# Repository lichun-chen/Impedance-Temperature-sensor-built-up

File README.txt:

//This project is the Final version code used in Z_T_sensor
The Z_T_sensor is designed to monitor the impedance and temperature of mortar samples installed in the field environments. Several multiplers, a real-time colock, a SD card is embaded into this circuit to get the real-time reading of the field samples.
License
OSU GENERAL PUBLIC LICENSE V1.0

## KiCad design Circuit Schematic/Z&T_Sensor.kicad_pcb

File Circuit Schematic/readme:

This is the circuit layout in KiCAD

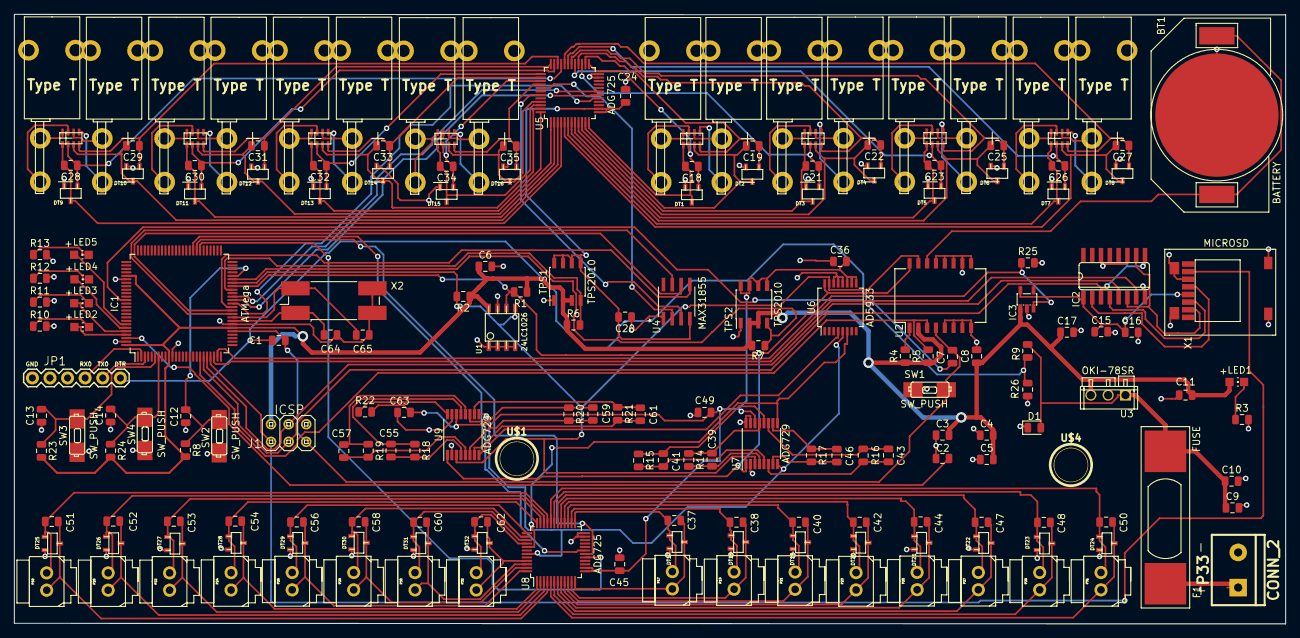
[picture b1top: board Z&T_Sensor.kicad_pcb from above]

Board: 2 copper layers, 183.6 x 88.0 mm, 196 parts (0 on the bottom side), 169 nets.

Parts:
BT1: BATTERY; Battery_20mm_coincell
C1, C2, C3, C4, C5, C6, C7, C8, C12, C13, C14, C15, C17: 0.1uF; C_0805_2012Metric
C9: 10u; C_0805_2012Metric
C10, C11: 0.1u; C_0805_2012Metric
C16: 10uF; C_0805_2012Metric
C18, C19, C20, C21, C22, C23, C24, C25, C26, C27, C28, C29, C30, C31, C32, C33, C34, C35, C36, C37, C38, C39, C40, C41, C42, C43, C44, C45, C46, C47, C48, C49, C50, C51, C52, C53, C54, C55, C56, C57, C58, C59, C60, C61, C62, C63: .01uF; C_0805_2012Metric
C64, C65: 22pF; C_0805_2012Metric
D1: DIODE; D_0805_2012Metric
DT1, DT2, DT3, DT4, DT5, DT6, DT7, DT8, DT9, DT10, DT11, DT12, DT13, DT14, DT15, DT16, DT17, DT18, DT19, DT20, DT21, DT22, DT23, DT24, DT25, DT26, DT27, DT28, DT29, DT30, DT31, DT32: TVSARRAY
F1: FUSE; FUSE_5x25
FB1, FB2, FB3, FB4, FB5, FB6, FB7, FB8: FEARRAY
IC1: ATMEGA2560-A; ATMega_TQFP-100_14x14mm_P0.5mm
IC2: 4050D; SO16
IC3: LP298XS; SOT23-5L
J1: ICSP; ICSP-pinhead-1-2X03
JP1: FTDI Basic; 1X06
LED1, LED2, LED3, LED4, LED5: LED; CHIP-LED0805
P1, P2, P3, P4, P5, P6, P7, P8, P9, P10, P11, P12, P13, P14, P15, P16: CONN_4; thermocouple-connector
P17, P18, P19, P20, P21, P22, P23, P24, P25, P26, P27, P28, P29, P30, P31, P32: CONN_2; Z_COMBICON2
P33: CONN_2; bornier2_V
R1, R2, R22, R26: 10K; R_0805_2012Metric
R3, R4, R5, R10, R11, R12, R13: 330; R_0805_2012Metric
R6, R7, R25: 100K; R_0805_2012Metric
R8, R9, R23, R24: 47k; R_0805_2012Metric
R14, R18: 560; R_0805_2012Metric
R15, R19: 1000; R_0805_2012Metric
R16, R20: 1500; R_0805_2012Metric
R17, R21: 2000; R_0805_2012Metric
SW1, SW2, SW3, SW4: SW_PUSH; SWITCH_2padsmd
TPS1, TPS2: TPS2010; TPS2010_SOIC-8-N8_3.9x4.9mm_P1.27mm
U1: 24LC1026
U2: DS3231; SOIC-16W_7.5x12.8mm_P1.27mm
U3: OKI-78SR
U4: MAX31855; MAX31855TASA&plus_T
U5, U8: ADG725; ADG725_TQFP-48-1EP_7x7mm_P0.5mm_EP3.5x3.5mm
U6: AD5933; AD5933_SSOP-16_5.3x6.2mm_P0.65mm
U7, U9: ADG729; ADG729_TSSOP-16_4.4x5mm_P0.65mm
U$1, U$4: FIDUCIAL; DrillHole_1pin
X1: MICROSD; MicroSD_2
X2: CRYSTAL; Crystal_SMD_SeikoEpson_MA506-4Pin_12.7x5.1mm

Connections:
+12V: F1.1, P33.1
/MISO: IC1.22, J1.1, X1.7
/MOSI: IC1.21, IC2.5, J1.4
/RX0: IC1.2, JP1.3
/SCK: IC1.20, IC2.3, IC2.9, J1.3
/SD_CS: IC1.23, IC2.7
/SD_Card/+3V3: C15.1, C16.1, IC2.1, IC3.5, X1.4
/SD_EN: IC1.24, IC3.3, R25.1
/Switch_LED/SWITCH1: C12.2, IC1.46, R8.1, SW2.2
/Switch_LED/SWITCH2: C13.2, IC1.6, R23.1, SW3.2
/Switch_LED/SWITCH3: C14.2, IC1.7, R24.1, SW4.2
/TX0: IC1.3, JP1.2
/T_sensor/5V: C20.2, C24.1, TPS1.5, TPS1.6, TPS1.7, TPS1.8, U4.4, U5.13, U5.14
/T_sensor/DIN: IC1.39, U5.18
/T_sensor/MISO: IC1.35, U4.7
/T_sensor/SCK: IC1.37, U4.5
/T_sensor/SCLK: IC1.40, U5.19
/T_sensor/SS: IC1.36, U4.6
/T_sensor/SYNC: IC1.38, U5.17
/T_sensor/ThermocoupleBreakout/T1a: FB1.5, P1.1
/T_sensor/ThermocoupleBreakout/T1b: FB1.6, P1.2
/T_sensor/ThermocoupleBreakout/T2a: FB1.7, P3.1
/T_sensor/ThermocoupleBreakout/T2b: FB1.8, P3.2
/T_sensor/ThermocoupleBreakout/T3a: FB2.5, P5.1
/T_sensor/ThermocoupleBreakout/T3b: FB2.6, P5.2
/T_sensor/ThermocoupleBreakout/T4a: FB2.7, P7.1
/T_sensor/ThermocoupleBreakout/T4b: FB2.8, P7.2
/T_sensor/ThermocoupleBreakout/T5a: FB3.5, P9.1
/T_sensor/ThermocoupleBreakout/T5b: FB3.6, P9.2
/T_sensor/ThermocoupleBreakout/T6a: FB3.7, P11.1
/T_sensor/ThermocoupleBreakout/T6b: FB3.8, P11.2
/T_sensor/ThermocoupleBreakout/T7a: FB4.5, P13.1
/T_sensor/ThermocoupleBreakout/T7b: FB4.6, P13.2
/T_sensor/ThermocoupleBreakout/T8a: FB4.7, P15.1
/T_sensor/ThermocoupleBreakout/T8b: FB4.8, P15.2
/T_sensor/ThermocoupleBreakout/T9a: FB5.5, P2.1
/T_sensor/ThermocoupleBreakout/T9b: FB5.6, P2.2
/T_sensor/ThermocoupleBreakout/T10a: FB5.7, P4.1
/T_sensor/ThermocoupleBreakout/T10b: FB5.8, P4.2
/T_sensor/ThermocoupleBreakout/T11a: FB6.5, P6.1
/T_sensor/ThermocoupleBreakout/T11b: FB6.6, P6.2
/T_sensor/ThermocoupleBreakout/T12a: FB6.7, P8.1
/T_sensor/ThermocoupleBreakout/T12b: FB6.8, P8.2
/T_sensor/ThermocoupleBreakout/T13a: FB7.5, P10.1
/T_sensor/ThermocoupleBreakout/T13b: FB7.6, P10.2
/T_sensor/ThermocoupleBreakout/T14a: FB7.7, P12.1
/T_sensor/ThermocoupleBreakout/T14b: FB7.8, P12.2
/T_sensor/ThermocoupleBreakout/T15a: FB8.5, P14.1
/T_sensor/ThermocoupleBreakout/T15b: FB8.6, P14.2
/T_sensor/ThermocoupleBreakout/T16a: FB8.7, P16.1
/T_sensor/ThermocoupleBreakout/T16b: FB8.8, P16.2
/Z_sensor/5V: C36.2, C45.2, C49.2, C63.2, R22.2, TPS2.5, TPS2.6, TPS2.7, TPS2.8, U6.9, U6.10, U6.11, U7.14, U8.13, U8.14, U9.14
/Z_sensor/DIN: IC1.58, U8.18
/Z_sensor/SCLK: IC1.59, U8.19
/Z_sensor/SYNC: IC1.57, U8.17
/Z_sensor/z_impedance/Z1A: C37.2, DT17.2, P17.1, U8.12
/Z_sensor/z_impedance/Z1B: C37.1, DT17.1, P17.2, U8.25
/Z_sensor/z_impedance/Z2A: C38.2, DT18.2, P19.1, U8.11
/Z_sensor/z_impedance/Z2B: C38.1, DT18.1, P19.2, U8.26
/Z_sensor/z_impedance/Z3A: C40.2, DT19.2, P21.1, U8.10
/Z_sensor/z_impedance/Z3B: C40.1, DT19.1, P21.2, U8.27
/Z_sensor/z_impedance/Z4A: C42.2, DT20.2, P23.1, U8.9
/Z_sensor/z_impedance/Z4B: C42.1, DT20.1, P23.2, U8.28
/Z_sensor/z_impedance/Z5A: C44.2, DT21.2, P25.1, U8.8
/Z_sensor/z_impedance/Z5B: C44.1, DT21.1, P25.2, U8.29
/Z_sensor/z_impedance/Z6A: C47.2, DT22.2, P27.1, U8.7
/Z_sensor/z_impedance/Z6B: C47.1, DT22.1, P27.2, U8.30
/Z_sensor/z_impedance/Z7A: C48.2, DT23.2, P29.1, U8.6
/Z_sensor/z_impedance/Z7B: C48.1, DT23.1, P29.2, U8.31
/Z_sensor/z_impedance/Z8A: C50.2, DT24.2, P31.1, U8.5
/Z_sensor/z_impedance/Z8B: C50.1, DT24.1, P31.2, U8.32
/Z_sensor/z_impedance/Z9A: C51.2, DT25.2, P18.1, U8.4
/Z_sensor/z_impedance/Z9B: C51.1, DT25.1, P18.2, U8.33
/Z_sensor/z_impedance/Z10A: C52.2, DT26.2, P20.1, U8.3
/Z_sensor/z_impedance/Z10B: C52.1, DT26.1, P20.2, U8.34
/Z_sensor/z_impedance/Z11A: C53.2, DT27.2, P22.1, U8.2
/Z_sensor/z_impedance/Z11B: C53.1, DT27.1, P22.2, U8.35
/Z_sensor/z_impedance/Z12A: C54.2, DT28.2, P24.1, U8.1
/Z_sensor/z_impedance/Z12B: C54.1, DT28.1, P24.2, U8.36
/Z_sensor/z_impedance/Z13A: C56.2, DT29.2, P26.1, U8.48
/Z_sensor/z_impedance/Z13B: C56.1, DT29.1, P26.2, U8.37
/Z_sensor/z_impedance/Z14A: C58.2, DT30.2, P28.1, U8.47
/Z_sensor/z_impedance/Z14B: C58.1, DT30.1, P28.2, U8.38
/Z_sensor/z_impedance/Z15A: C60.2, DT31.2, P30.1, U8.46
/Z_sensor/z_impedance/Z15B: C60.1, DT31.1, P30.2, U8.39
/Z_sensor/z_impedance/Z16A: C62.2, DT32.2, P32.1, U8.45
/Z_sensor/z_impedance/Z16B: C62.1, DT32.1, P32.2, U8.40
/clock-ISP schema/INTSQW: IC1.19, R5.2, U2.3
/led/LED1: IC1.97, LED2.A
/led/LED2: IC1.96, LED3.A
/led/LED3: IC1.95, LED4.A
/led/LED4: IC1.94, LED5.A
ADBATT: IC1.87, R9.1, R26.2
DTR: C1.2, C7.2, JP1.1
GND: BT1.2, C2.2, C3.1, C4.1, C5.1, C6.2, C8.2, C9.2, C10.2, C11.2, C12.1, C13.1, C14.1, C15.2, C16.2, C17.2, C20.1, C24.2, C36.1, C45.1, C49.1, C63.1, C64.2, C65.2, D1.1, DT1.3, DT2.3, DT3.3, DT4.3, DT5.3, DT6.3, DT7.3, DT8.3, DT9.3, DT10.3, DT11.3, DT12.3, DT13.3, DT14.3, DT15.3, DT16.3, DT17.3, DT18.3, DT19.3, DT20.3, DT21.3, DT22.3, DT23.3, DT24.3, DT25.3, DT26.3, DT27.3, DT28.3, DT29.3, DT30.3, DT31.3, DT32.3, IC1.11, IC1.32, IC1.81, IC1.99, IC2.8, IC2.11, IC2.14, IC3.2, J1.6, JP1.6, P1.3, P1.4, P2.3, P2.4, P3.3, P3.4, P4.3, P4.4, P5.3, P5.4, P6.3, P6.4, P7.3, P7.4, P8.3, P8.4, P9.3, P9.4, P10.3, P10.4, P11.3, P11.4, P12.3, P12.4, P13.3, P13.4, P14.3, P14.4, P15.3, P15.4, P16.3, P16.4, P33.2, R3.2, R10.2, R11.2, R12.2, R13.2, R25.2, R26.1, SW1.1, SW2.1, SW3.1, SW4.1, TPS1.1, TPS2.1, U1.1, U1.2, U1.3, U1.4, U1.7, U2.5, U2.6, U2.7, U2.8, U2.9, U2.10, U2.11, U2.12, U2.13, U3.2, U4.1, U5.23, U5.24, U6.12, U6.13, U6.14, U7.2, U7.15, U7.16, U8.23, U8.24, U9.2, U9.15, X1.6, X1.GND1, X1.GND2, X1.GND3, X1.GND4, X2.2, X2.3
unnamed: BT1.1, U2.14
unnamed: C2.1, IC1.98
unnamed: C9.1, C10.1, D1.2, F1.2, R9.2, U3.1
unnamed: C18.1, DT1.1, FB1.2, U5.25
unnamed: C18.2, DT1.2, FB1.1, U5.12
unnamed: C19.1, DT2.1, FB1.4, U5.26
unnamed: C19.2, DT2.2, FB1.3, U5.11
unnamed: C21.1, DT3.1, FB2.2, U5.27
unnamed: C21.2, DT3.2, FB2.1, U5.10
unnamed: C22.1, DT4.1, FB2.4, U5.28
unnamed: C22.2, DT4.2, FB2.3, U5.9
unnamed: C23.1, DT5.1, FB3.2, U5.29
unnamed: C23.2, DT5.2, FB3.1, U5.8
unnamed: C25.1, DT6.1, FB3.4, U5.30
unnamed: C25.2, DT6.2, FB3.3, U5.7
unnamed: C26.1, DT7.1, FB4.2, U5.31
unnamed: C26.2, DT7.2, FB4.1, U5.6
unnamed: C27.1, DT8.1, FB4.4, U5.32
unnamed: C27.2, DT8.2, FB4.3, U5.5
unnamed: C28.1, DT9.1, FB5.2, U5.33
unnamed: C28.2, DT9.2, FB5.1, U5.4
unnamed: C29.1, DT10.1, FB5.4, U5.34
unnamed: C29.2, DT10.2, FB5.3, U5.3
unnamed: C30.1, DT11.1, FB6.2, U5.35
unnamed: C30.2, DT11.2, FB6.1, U5.2
unnamed: C31.1, DT12.1, FB6.4, U5.36
unnamed: C31.2, DT12.2, FB6.3, U5.1
unnamed: C32.1, DT13.1, FB7.2, U5.37
unnamed: C32.2, DT13.2, FB7.1, U5.48
unnamed: C33.1, DT14.1, FB7.4, U5.38
unnamed: C33.2, DT14.2, FB7.3, U5.47
unnamed: C34.1, DT15.1, FB8.2, U5.39
unnamed: C34.2, DT15.2, FB8.1, U5.46
unnamed: C35.1, DT16.1, FB8.4, U5.40
unnamed: C35.2, DT16.2, FB8.3, U5.45
unnamed: C39.1, R14.2, U7.4
unnamed: C39.2, R14.1, U7.13
unnamed: C41.1, R15.2, U7.5
unnamed: C41.2, R15.1, U7.12
unnamed: C43.1, R16.2, U7.6
unnamed: C43.2, R16.1, U7.11
unnamed: C46.1, R17.2, U7.7
unnamed: C46.2, R17.1, U7.10
unnamed: C55.1, R18.2, U9.4
unnamed: C55.2, R18.1, U9.13
unnamed: C57.1, R19.2, U9.5
unnamed: C57.2, R19.1, U9.12
unnamed: C59.1, R20.2, U9.6
unnamed: C59.2, R20.1, U9.11
unnamed: C61.1, R21.2, U9.7
unnamed: C61.2, R21.1, U9.10
unnamed: C64.1, IC1.33, X2.1
unnamed: C65.1, IC1.34, X2.4
unnamed: IC1.42, R6.2, TPS1.4
unnamed: IC1.45, R7.2, TPS2.4
unnamed: IC2.2, X1.5
unnamed: IC2.4, X1.3
unnamed: IC2.6, IC2.10, X1.2
unnamed: LED1.C, R3.1
unnamed: LED2.C, R10.1
unnamed: LED3.C, R11.1
unnamed: LED4.C, R12.1
unnamed: LED5.C, R13.1
unnamed: R4.2, U2.1
unnamed: R22.1, U9.16
unnamed: U4.2, U5.41
unnamed: U4.3, U5.43
unnamed: U6.4, U9.8
unnamed: U6.5, U7.8, U8.43, U9.9
unnamed: U6.6, U7.9, U8.41
RESET: C1.1, C7.1, IC1.30, J1.5, SW1.2, U2.4
SCL: IC1.43, R1.2, U1.6, U2.16, U6.16, U7.1, U9.1
SDA: IC1.44, R2.2, U1.5, U2.15, U6.15, U7.3, U9.3
V1: C3.2, C4.2, C5.2, C6.1, C8.1, C11.1, C17.1, IC1.10, IC1.31, IC1.80, IC1.100, IC3.1, J1.2, LED1.A, R1.1, R2.1, R4.1, R5.1, R6.1, R7.1, R8.2, R23.2, R24.2, TPS1.2, TPS1.3, TPS2.2, TPS2.3, U1.8, U2.2, U3.3

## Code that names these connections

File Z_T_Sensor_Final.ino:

//*******************************************************************************************************************************************
#include "AD5933.h"
#include "Adafruit_MAX31855.h"
#include <Wire.h>
#include <SD.h>
#include <SPI.h>
#include "Z_T_functions.h"

//*******************************************************************************************************************************************
//******************************************DEFINE Z&T measurement part**********************************************************************
Adafruit_MAX31855 THERMOcouple(MAXCLK, MAXCS, MAXDO);
Z_T_functions_Class Z_T_func;

//*******************************************************************************************************************************************
//******************************************DEFINE ADG725 code*******************************************************************************
int pinoff=128;//code to turn off all the switches of ADG725 (16 ports)
int SWITCHnum = 0;
int CALIBnum = 1;

//*******************************************************************************************************************************************
//******************************************DEFINE Battery part******************************************************************************
int BATT_VOLT = 0;

//*******************************************************************************************************************************************
//*******************************************************************************************************************************************
void setup()
{
  Wire.begin();        // join i2c bus (address optional for master)   
  Serial.begin(9600);
  while (!Serial) delay(1); // wait for Serial on Leonardo/Zero, etc

  //set the pins for LEDS
  pinMode(LED2, OUTPUT);
  pinMode(LED3, OUTPUT);
  pinMode(LED4, OUTPUT);
  pinMode(LED5, OUTPUT);
  digitalWrite(LED2, LOW);
  digitalWrite(LED3, LOW);
  digitalWrite(LED4, LOW);
  digitalWrite(LED5, LOW);
  
  //set pin mode for multiplexers_resistors
  pinMode(SS_Z, OUTPUT);
  pinMode(SCLK_Z, OUTPUT); 
  pinMode(MOSI_Z, OUTPUT);
  //set the pin mode for multiplexer_temperature
  pinMode(SS_T, OUTPUT);
  pinMode(SCLK_T, OUTPUT); 
  pinMode(MOSI_T, OUTPUT);
  
  //SD Card Initialization
  pinMode(SDCard_EN,OUTPUT);// enable voltage converter (define as asigned in the KiCAD file)
  digitalWrite(SDCard_EN, HIGH);// enable voltage converter (define as asigned in the KiCAD file)
  pinMode(SD_CS,OUTPUT); 
  //SD card can be only initialized once, multiple initializations result to failure. so must leave this part in the setup function, not in the loop function.
  if (!SD.begin(SD_CS))
    { // if the SD card is not put right, then do nothing
      Serial.println("SD Card Initialization Failed!"); 
      digitalWrite(LED4,HIGH); // Turn on the LED4 as a sign for SD card failed.
    }

  //set TPS2010 EN pin
  pinMode(TPSEN_Z, OUTPUT);
  pinMode(TPSEN_T, OUTPUT);
  //TUEN OFF THE TPS2010 SWITCH at the setup beginning
  digitalWrite(TPSEN_Z, HIGH); // LOW turns on the power; High turns off the power
  digitalWrite(TPSEN_T, HIGH); // LOW turns on the power; High turns off the power
  
  delay(100);
}
//*****************************************************************************************************************************************************
void loop()
{
  // GET THE VOLTAGE OF THE BATTERY AT THE BEGINNING OF EACH LOOP
  BATT_VOLT = Z_T_func.Batt_analogread();
  if (BATT_VOLT < Batt_Low) // if the battery is low then do nothing
  {delay(1800000); /*delay 30mins */ }
  else {     
      //****************************************************************************************************************************************************
      //Turn on TPS2010 switch. set the EN pin for TPSEN_Z, TPSEN_T
      digitalWrite(TPSEN_Z, LOW); // LOW turns on the power; High turns off the power
      digitalWrite(TPSEN_T, LOW); // LOW turns on the power; High turns off the power
              
      //close all switch pins of ADG729 before measurement
      Z_T_func.SwiChoi_Z(0, ADDRESS_SwiCalib);// close all switch pins of impedance calibration
      Z_T_func.SwiChoi_Z(0, ADDRESS_SwiRFB);// close all switch pins of RFB resistor
      //close all switch pins of ADG725 (16 ports) before measurement
      Z_T_func.Switch_Z(pinoff);
      Z_T_func.Switch_T(pinoff);
  
      // set the initial time here:only run this part once
      // NOTE: This part must be put after the function of an I2C device (ADG729 here), otherwise the clock will not work
      // DS3231 seconds, minutes, hours, day, date, month, year
      //Z_T_func.setDS3231time(30,57,17,1,25,8,19); 
            
      //Turn off all the LEDS befores measurement. start measuring impedance&temperature SIGN
      digitalWrite(LED2,LOW);
      digitalWrite(LED3,LOW);
      digitalWrite(LED4,LOW);
      digitalWrite(LED5,LOW);
      //************************************Measure Battery ***********************************************************************************************
      Z_T_func.Batt_Volt();
      //************************************Measure Impedance***********************************************************************************************    
      // start measure the calibration resistors
      for (CALIBnum = 1; CALIBnum <5; CALIBnum ++){
          Z_T_func.SwiChoi_Z(CALIBnum, ADDRESS_SwiCalib);
          Z_T_func.impeTest(0,CALIBnum, LED2);//LED2 will blink when it is measuring
      }
      //close all pins of calibration ports
      Z_T_func.SwiChoi_Z(0, ADDRESS_SwiCalib); // close all switch pins of impedance calibration
              
      // start measure impedance with different switchnum.
      for (SWITCHnum = 0; SWITCHnum < 16; SWITCHnum ++) {  
          Z_T_func.Switch_Z(SWITCHnum);
          Z_T_func.impeTest(1, SWITCHnum, LED2);//LED2 will blink when it is measuring
      }
      //close all pins of switch_resistor
      Z_T_func.Switch_Z(pinoff);
              
      delay(100);//delay 0.1s
      //***********************************Measure Temperature**********************************************************************************************
      // start measure temperature with different switchnum.
      for (SWITCHnum = 0; SWITCHnum <8 ; SWITCHnum ++) {
          Z_T_func.Switch_T(SWITCHnum);
          Z_T_func.tempTest(SWITCHnum, LED2, THERMOcouple); // LED2 will blink when it is measuring
      }
      //close all pins of switch_temperature
      Z_T_func.Switch_T(pinoff);
              
      delay(100);//delay 0.1s
      //****************************************************************************************************************************************************
      //TUEN OFF THE TPS2010 SWITCH AFTER MEASUREMENT
      digitalWrite(TPSEN_Z, HIGH); // LOW turns on the power; High turns off the power
      digitalWrite(TPSEN_T, HIGH); // LOW turns on the power; High turns off the power
      
      delay(1800000); //delay 30mins
       
  }
}

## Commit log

2021-04-01 Z_T_sensor development
    This is a sensor design project which combines AD5933 and MAX31855 with multiplexers. This sensor is designed to monitor the impedance and temperature of the mortar sample under filed environments.
2021-04-01 schematics of the circuit board
2021-04-02 Create Circuit Schematic

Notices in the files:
parts and their libraries:
Copyright 2016 Accelerated Designs. All rights reserved.
